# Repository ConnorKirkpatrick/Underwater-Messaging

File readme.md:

# Underwater messaging system

This project emcompases the creation of a custom underwater messaging system utilising COTS hardware.

Sources:
* [SoundFi: Transmitting Data Using Sound (Ultrasonic Sound)](https://community.element14.com/challenges-projects/project14/acoustics/b/blog/posts/soundfi---transmitting-data-using-sound-ultrasonic-sound)
* [Hackerday: Dead Simple Ultrasonic Data Communication](https://hackaday.com/2018/06/01/dead-simple-ultrasonic-data-communication/)

BOM
* [Piezo discs for transducer](https://www.amazon.co.uk/dp/B0BX46WMJH?ref=ppx_yo2ov_dt_b_fed_asin_title)

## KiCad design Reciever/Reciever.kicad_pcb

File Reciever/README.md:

# Reciever

Small POC reciever board to amplify the returned signal from a Piezo-Eletric Disc so that we might be able to derive a signal

# Schematic 

# PCB

# Model

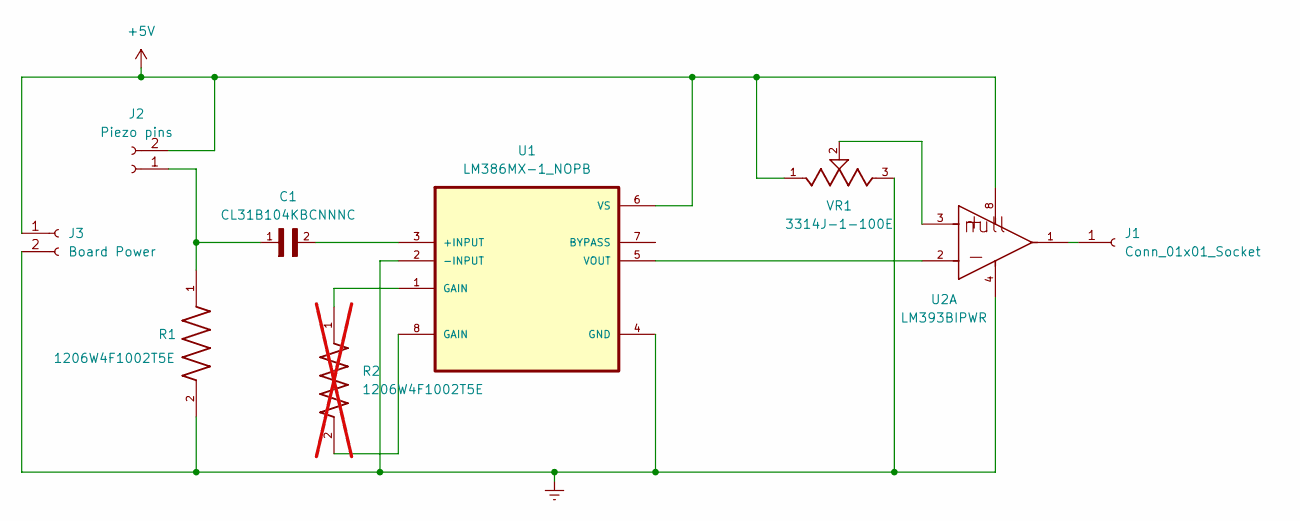
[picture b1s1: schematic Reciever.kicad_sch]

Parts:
C1: CL31B104KBCNNNC; CAPC3216X100N
J1: Conn_01x01_Socket; SolderWire-0.1sqmm_1x01_D0.4mm_OD1mm
J2: Piezo pins; SolderWire-0.5sqmm_1x02_P4.6mm_D0.9mm_OD2.1mm
J3: Board Power; SolderWire-0.1sqmm_1x02_P3.6mm_D0.4mm_OD1mm
R1: 1206W4F1002T5E; RESC3115X65N; PARTREV V3
R2: 1206W4F1002T5E; RESC3115X65N; PARTREV V3; not fitted
U1: LM386MX-1_NOPB; SOIC127P599X175-8N
U2: LM393BIPWR; PW0008A-IPC_A; PARTNUMBER LM393BIPWR; DigiKey_Part_Number 296-LM393BIPWRCT-ND
VR1: 3314J-1-100E; TRIM_3314J-1-100E

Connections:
+5V: J2.2, J3.1, U1.6 (VS), U2.8, VR1.1
GND: J3.2, R1.2, U1.2 (-INPUT), U1.4 (GND), U2.4, VR1.3
unnamed: J1.1, U2.1
unnamed: C1.1, J2.1, R1.1
unnamed: R2.1, U1.1 (GAIN)
unnamed: R2.2, U1.8 (GAIN)
unnamed: C1.2, U1.3 (+INPUT)
unnamed: U1.5 (VOUT), U2.2
unnamed: U2.3, VR1.2

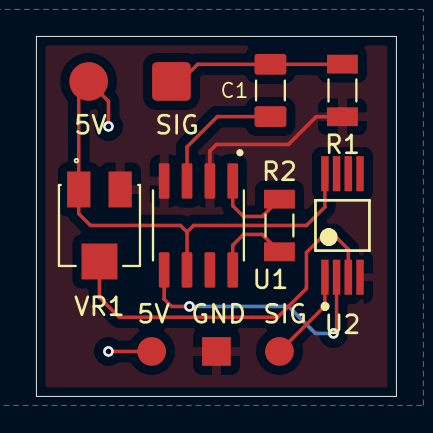
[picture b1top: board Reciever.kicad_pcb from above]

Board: 2 copper layers, 20.0 x 20.0 mm, 9 parts (0 on the bottom side), 9 nets.

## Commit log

2025-10-06 Initial commit with Reciever schematic
2025-10-06 updated to utilise more common parts
2025-10-06 updated pcb, removed dead traces
2025-10-06 Added images to the readme
2025-10-06 Updated to add resistor pad for gain, and 5v flood to CL2
